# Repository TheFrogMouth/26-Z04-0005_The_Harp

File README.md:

# 26-Z04-0005 — The Harp

Frogmouth digital sympathetic-string guitar pedal. Up to 24 modelled strings
that nobody plays ring when the guitar sounds their note, retuned continuously
to the chord being played. STM32H750VBT6, AK4621EF codec, no SDRAM, relay
bypass, in a Hammond 125B on the Alchemist/Relic board and jack layout.

Status: **first schematic draft, board placed and mostly routed, 29 connections open.** Seven sheets generated from the Timekeeper's circuits and The Relic's bypass (190 parts, net-traced, drawn to the Frogmouth schematic standard, not yet opened in KiCad); board outline and 28 face/jack/bypass footprints placed from The Relic. Stereo in (TRS) and a 0.91 in OLED display added 2026-10-08; the PCB was synced to the schematic and every part placed on both sides on 2026-10-08 (scripted; one-board fit confirmed, see `docs/pcb-plan.md` *Placement*). First routing pass by script on 2026-10-09: GND to In1 and rails on In2 from every pad, analog and digital kept apart. Opened in KiCad 2026-10-10 (now the source of truth): power section re-placed and re-routed, every track at the Alchemist widths and at 0/45/90°, 29 connections left for KiCad (*Routing*). See `docs/pcb-plan.md` and `kicad/README.md`.

## Layout

| Path | Contents |
|------|----------|
| `docs/design-brief.md` | What the pedal is, engine, controls, bypass, cost target, decisions, open items |
| `docs/pcb-plan.md` | One-board plan and two-board fallback, face schedule, zoning, schematic sheets, pin budget, order of work |
| `docs/firmware-requirements.md` | Firmware requirements (draft): audio path, engine, controls, display, bypass, persistence, budgets, verification |
| `kicad/the_harp/` | KiCad 10 project: seven-sheet schematic, Relic-outline board |
| `Gerbers/` | Fabrication output, when generated |
| `firmware/the_harp/` | STM32H750 firmware |
| `Documents/` | Controlled LaTeX documents, one folder each |
| `bom/` | Generated BOM (`scripts/export_bom.py`, to be adapted from The Relic) |
| `scripts/harp_schematic/` | Schematic generator and net checker (first draft only; see its README) |
| `scripts/pcb_placement/` | PCB sync to the schematic and scripted placement (2026-10-08; see its README) |
| `scripts/oled_drawings/` | Face cut-out and OLED-to-PCB drawings in `docs/images/` |

The layout is the Frogmouth product repository standard
(`docs/repo-structure.md` in 26-F01-0001_Frogmouth).

## Conventions

Same as The Relic and The Alchemist: enclosure centre is the PCB drill/place
and grid origin at (148.5, 105); face X right, face Y up; jacks on the board
underside at the Alchemist's positions and heights; pots on the board;
momentary footswitches wired to pads; relay true bypass.

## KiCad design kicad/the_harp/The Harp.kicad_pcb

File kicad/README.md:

# KiCad project — The Harp

`the_harp/` is the KiCad 10 project. The board was seeded from The Relic
(2026-10-04); the schematic is **generated** by
`scripts/harp_schematic/build_layout.py` from the circuits of the Timekeeper
DSP board and The Relic's relay bypass (`harp_spec.py`) and a hand layout per
sheet (`layouts/`), drawn to the Frogmouth schematic standard
(`docs/schematic-standard.md` in 26-F01-0001_Frogmouth, 2026-10-07). Nothing
here has been opened in KiCad yet: run ERC first.

## Sheets

| Sheet | File |
|---|---|
| Root | `The Harp.kicad_sch` |
| Controls and LEDs | `Controls and LEDs.kicad_sch` |
| MCU (STM32H750VBT6, W25Q128) | `MCU.kicad_sch` |
| Power | `Power.kicad_sch` |
| Jacks and Bypass | `Jacks and Bypass.kicad_sch` |
| Codec (AK4621EF) | `Codec.kicad_sch` |
| ADC Driver (THS4522) | `ADC Driver.kicad_sch` |
| Analog In and Out (OPA1656, OPA1688) | `Analog In and Out.kicad_sch` |

What each sheet holds, the pin map and the deliberate differences from the
Timekeeper are in `docs/pcb-plan.md`. The Relic's `Power and IO` sheet is
gone: its relay bypass is redrawn on Jacks and Bypass with the same
designators, and its regulators are replaced by the Timekeeper's buck and LDO.

## Board

The Relic's 56 × 90 mm outline with the DC tab, four-layer stack, GND zone
and 125B guides. 26 footprints are placed: the four pots, three toggles, the
effect LED, the five jacks (DC, IN, OUT L, OUT R, EXP), the relay and its
driver, the effect-LED driver and the bypass footswitch pads. The four
1/4 in jacks and the relay were replaced on 2026-10-05 with The Alchemist's
NMJ6HCD2 and G6K-2F-Y footprints at its positions. On 2026-10-06 the face
moved to The Alchemist's layout: RV104 and RV106 removed, the three toggles
on the Taiway 100-DP6 footprint at (−20, +13), (0, −5) and (+20, +13) (Retune moved to (0, −24) on 2026-10-09), the
bypass footswitch on hand-solder pads, and R405 / D402 moved off J403's
rear pads. The Relic's
regulator parts (C401–C407, D401, R401–R403, U401, U402) were removed. On
2026-10-08 the board was synced to the schematic (see step 2 below): every
footprint is linked to its symbol with its pad nets, the twelve note LEDs
and their resistors are gone. All 181 footprints were then placed on the
top side by script (`scripts/pcb_placement/`, `docs/pcb-plan.md` *Placement*).

## First steps in KiCad

1. Open `The Harp.kicad_pro`, open every sheet once, run ERC. Expect
   cosmetic warnings (label placement, overlapping text); anything about
   power pins or unconnected pins is real, report it.
2. The board was synced to the schematic on 2026-10-08 without KiCad (no
   KiCad in that session): 181 footprints (190 symbol units), each linked to its symbol, values
   and pad nets checked pin by pin against `harp_spec.py`. Run Tools → Update PCB from
   Schematic once anyway: it should report no changes apart from net
   renames (KiCad names unlabelled nets `Net-(...)`) and footprint library
   refreshes. Anything else it reports is a sync miss: note it.
3. Every part is placed on both sides (scripted, 2026-10-08; see *Placement*
   in `docs/pcb-plan.md`). Look it over, then run DRC.
4. The board was routed by script on 2026-10-09 (`scripts/pcb_routing/`,
   *Routing* in `docs/pcb-plan.md`): GND vias per the Relic rule, rails on
   In2. On 2026-10-10 the power section was re-placed and re-routed and
   every track brought to the Alchemist widths (0.254 / 0.508 / 0.762 /
   1.0 mm, digital 0.1524) and to 0/45/90°. Fill the In1 GND zone (B), finish the 29 open
   connections listed there, then DRC. The net classes (GND, Rail, Power,
   Audio, Digital, Control, clearance 0.1524) are in the project.

Once the schematic has been edited in KiCad, the KiCad files are the source
of truth; do not re-run the generator over them (see
`scripts/harp_schematic/README.md`).

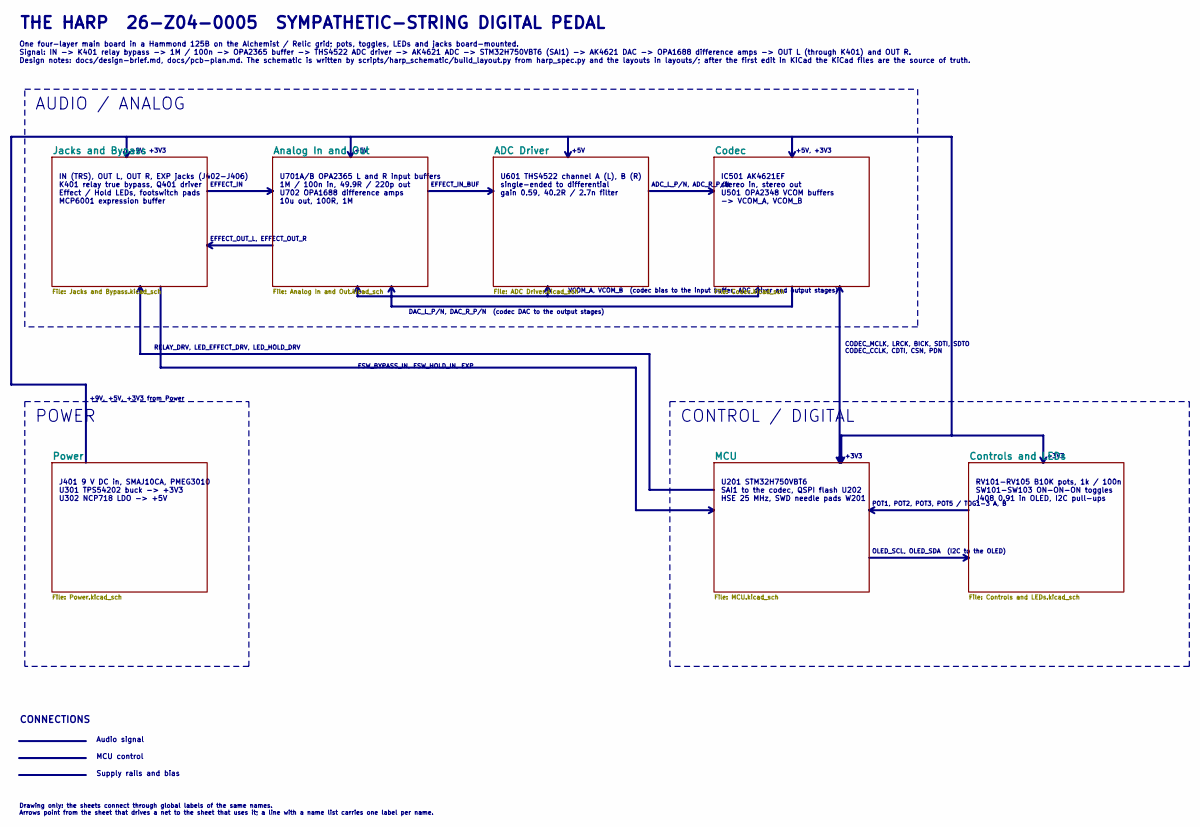
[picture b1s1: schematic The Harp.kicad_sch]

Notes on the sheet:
RELAY_DRV, LED_EFFECT_DRV, LED_HOLD_DRV
+5V, +3V3
J401 9 V DC in, SMAJ10CA, PMEG3010 U301 TPS54202 buck -> +3V3 U302 NCP718 LDO -> +5V
CONTROL / DIGITAL
+5V
EFFECT_OUT_L, EFFECT_OUT_R
DAC_L_P/N, DAC_R_P/N (codec DAC to the output stages)
THE HARP 26-Z04-0005 SYMPATHETIC-STRING DIGITAL PEDAL
FSW_BYPASS_IN, FSW_HOLD_IN, EXP
+9V, +5V, +3V3 from Power
Supply rails and bias
IC501 AK4621EF stereo in, stereo out U501 OPA2348 VCOM buffers -> VCOM_A, VCOM_B
POT1, POT2, POT3, POT5 / TOG1-3 A, B
EFFECT_IN_BUF
U601 THS4522 channel A (L), B (R) single-ended to differential gain 0.59, 40.2R / 2.7n filter
OLED_SCL, OLED_SDA (I2C to the OLED)
U701A/B OPA2365 L and R input buffers 1M / 100n in, 49.9R / 220p out U702 OPA1688 difference amps 10u out, 100R, 1M
Audio signal
+9V, +3V3
One four-layer main board in a Hammond 125B on the Alchemist / Relic grid; pots, toggles, LEDs and jacks board-mounted. Signal: IN -> K401 relay bypass -> 1M / 100n -> OPA2365 buffer -> THS4522 ADC driver -> AK4621 ADC -> STM32H750VBT6 (SAI1) -> AK4621 DAC -> OPA1688 difference amps -> OUT L (throu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
+3V3
U201 STM32H750VBT6 SAI1 to the codec, QSPI flash U202 HSE 25 MHz, SWD needle pads W201
MCU control
CODEC_MCLK, LRCK, BICK, SDTI, SDTO CODEC_CCLK, CDTI, CSN, PDN
POWER
IN (TRS), OUT L, OUT R, EXP jacks (J402-J406) K401 relay true bypass, Q401 driver Effect / Hold LEDs, footswitch pads MCP6001 expression buffer
RV101-RV105 B10K pots, 1k / 100n SW101-SW103 ON-ON-ON toggles J408 0.91 in OLED, I2C pull-ups
AUDIO / ANALOG
EFFECT_IN
VCOM_A, VCOM_B (codec bias to the input buffer, ADC driver and output stages)
CONNECTIONS
ADC_L_P/N, ADC_R_P/N
Drawing only: the sheets connect through global labels of the same names. Arrows point from the sheet that drives a net to the sheet that uses it; a line with a name list carries one label per name.

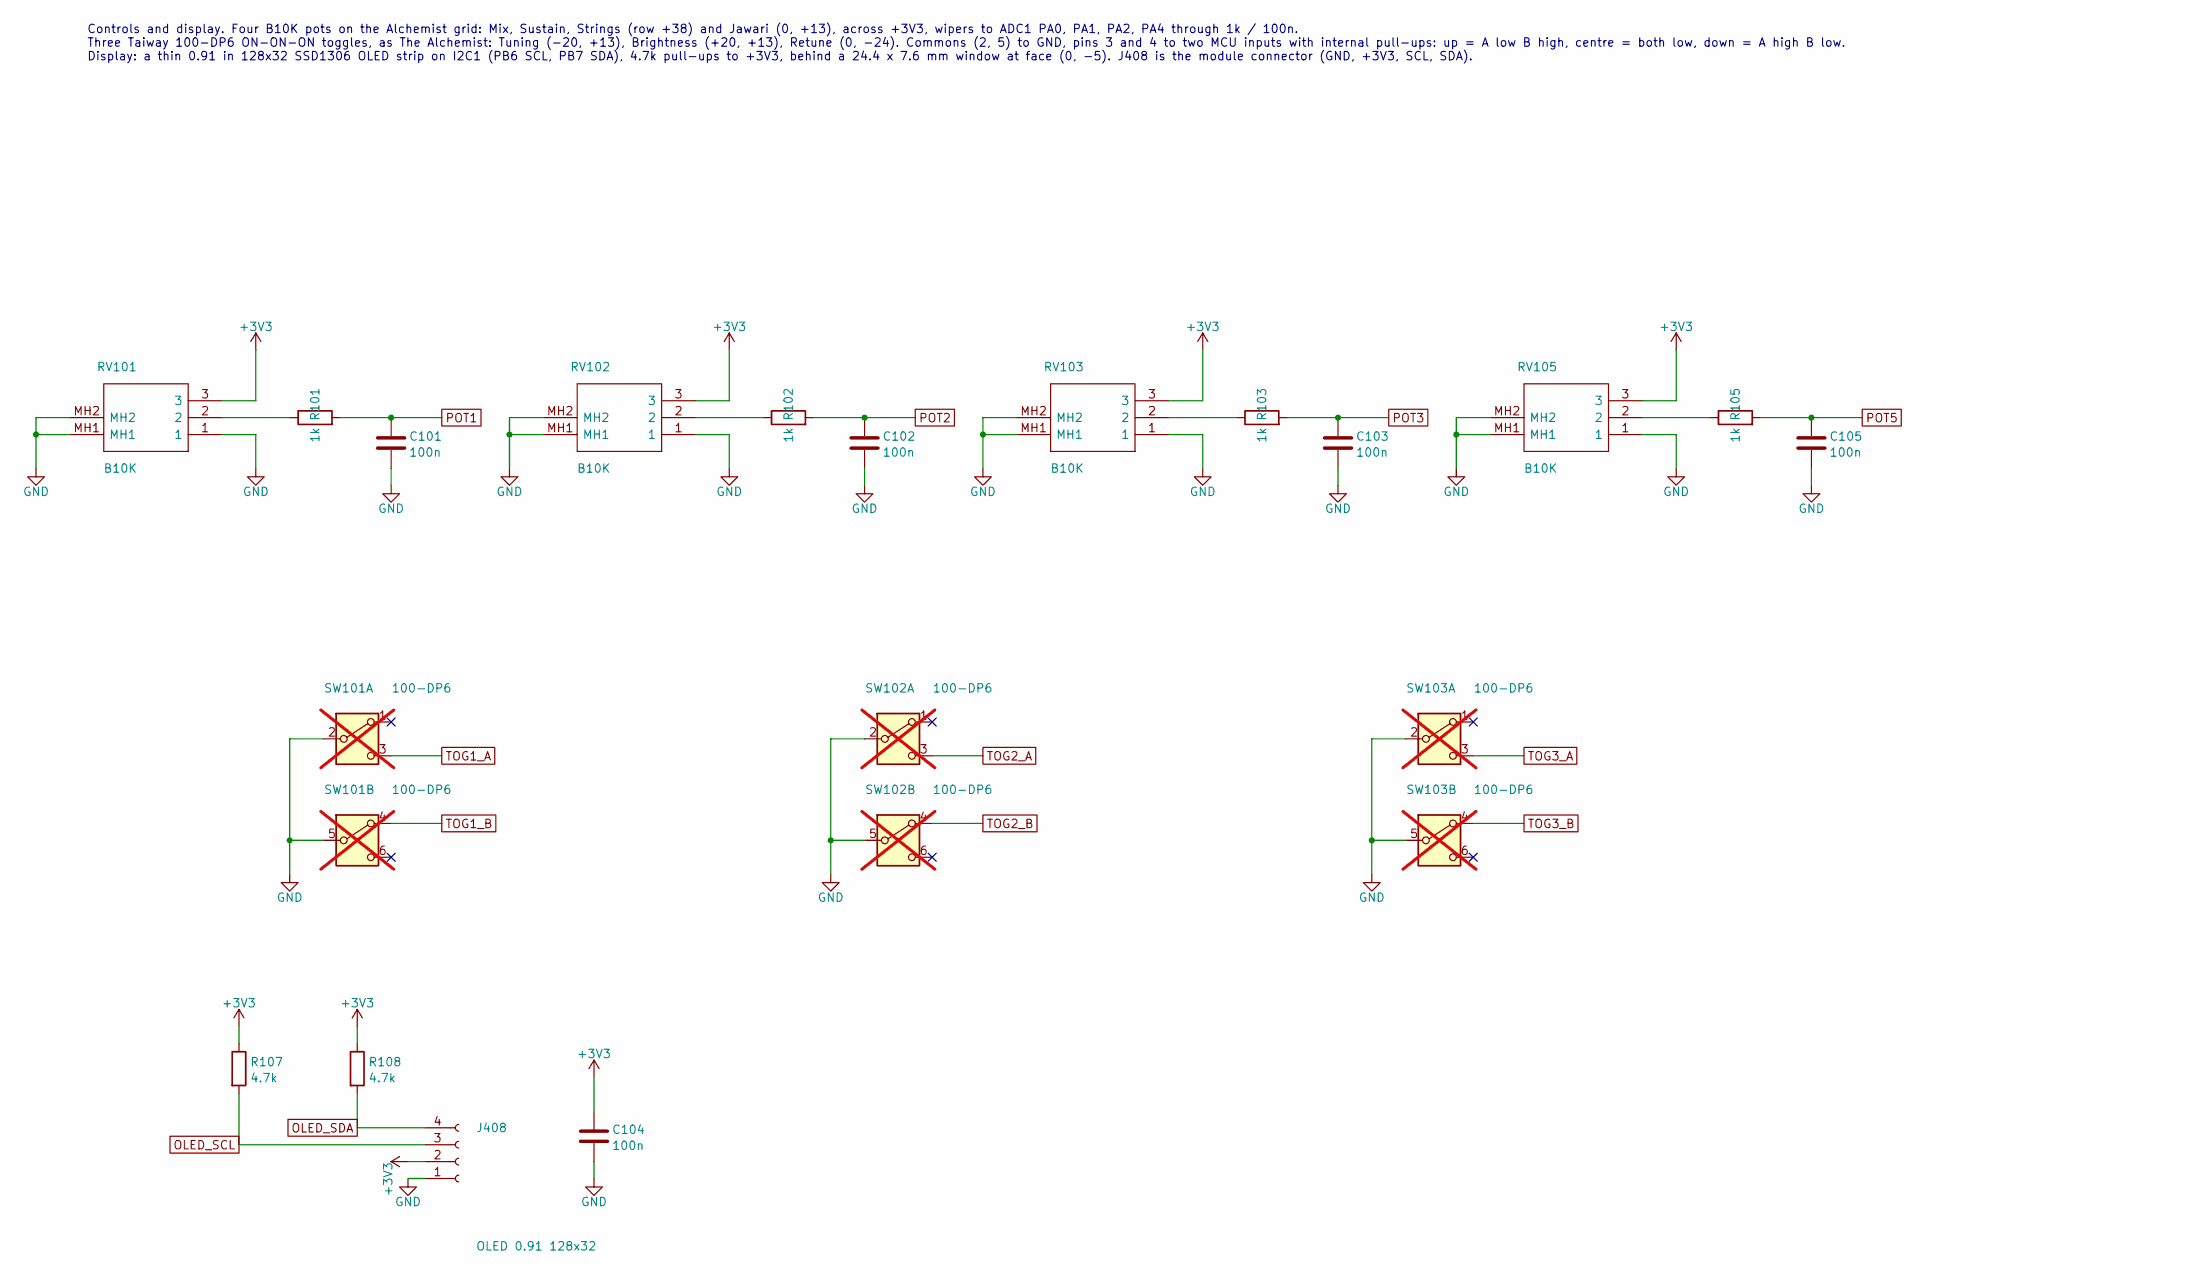
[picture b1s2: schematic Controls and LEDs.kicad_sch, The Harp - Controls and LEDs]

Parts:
C101, C102, C103, C104, C105: 100n; C_0603_1608Metric
J408: OLED 0.91 128x32; JST_SH_SM04B-SRSS-TB_1x04-1MP_P1.00mm_Horizontal; Mfg Part # SM04B-SRSS-TB
R101, R102, R103, R105: 1k; R_0603_1608Metric
R107, R108: 4.7k; R_0603_1608Metric
RV101, RV102, RV103, RV105: B10K; RD901F4015R1B10K00DL1; Mfg Part # RD901F-40-15R1-B10K; LCSC C20619174
SW101, SW102, SW103: 100-DP6; 100DP3T1B2M2QE; Mfg Part # 100-DP6-T200B1M2QE; not fitted

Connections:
+3V3: C104.1, J408.2, R107.1, R108.1, RV101.3, RV102.3, RV103.3, RV105.3; also elsewhere on the board
GND: C101.2, C102.2, C103.2, C104.2, C105.2, J408.1, RV101.1, RV101.MH1, RV101.MH2, RV102.1, RV102.MH1, RV102.MH2, RV103.1, RV103.MH1, RV103.MH2, RV105.1, RV105.MH1, RV105.MH2, SW101.2 (B), SW101.5 (B), SW102.2 (B), SW102.5 (B), SW103.2 (B), SW103.5 (B); also elsewhere on the board
unnamed: R101.1, RV101.2
unnamed: R102.1, RV102.2
unnamed: R103.1, RV103.2
unnamed: R105.1, RV105.2
OLED_SCL: J408.3, R107.2; also elsewhere on the board
OLED_SDA: J408.4, R108.2; also elsewhere on the board
POT1: C101.1, R101.2; also elsewhere on the board
POT2: C102.1, R102.2; also elsewhere on the board
POT3: C103.1, R103.2; also elsewhere on the board
POT5: C105.1, R105.2; also elsewhere on the board
TOG1_A: SW101.3 (C); also elsewhere on the board
TOG1_B: SW101.4 (A); also elsewhere on the board
TOG2_A: SW102.3 (C); also elsewhere on the board
TOG2_B: SW102.4 (A); also elsewhere on the board
TOG3_A: SW103.3 (C); also elsewhere on the board
TOG3_B: SW103.4 (A); also elsewhere on the board

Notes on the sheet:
Controls and display. Four B10K pots on the Alchemist grid: Mix, Sustain, Strings (row +38) and Jawari (0, +13), across +3V3, wipers to ADC1 PA0, PA1, PA2, PA4 through 1k / 100n. Three Taiway 100-DP6 ON-ON-ON toggles, as The Alchemist: Tuning (-20, +13), Brightness (+20, +13), Retune (0, -24). Comm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

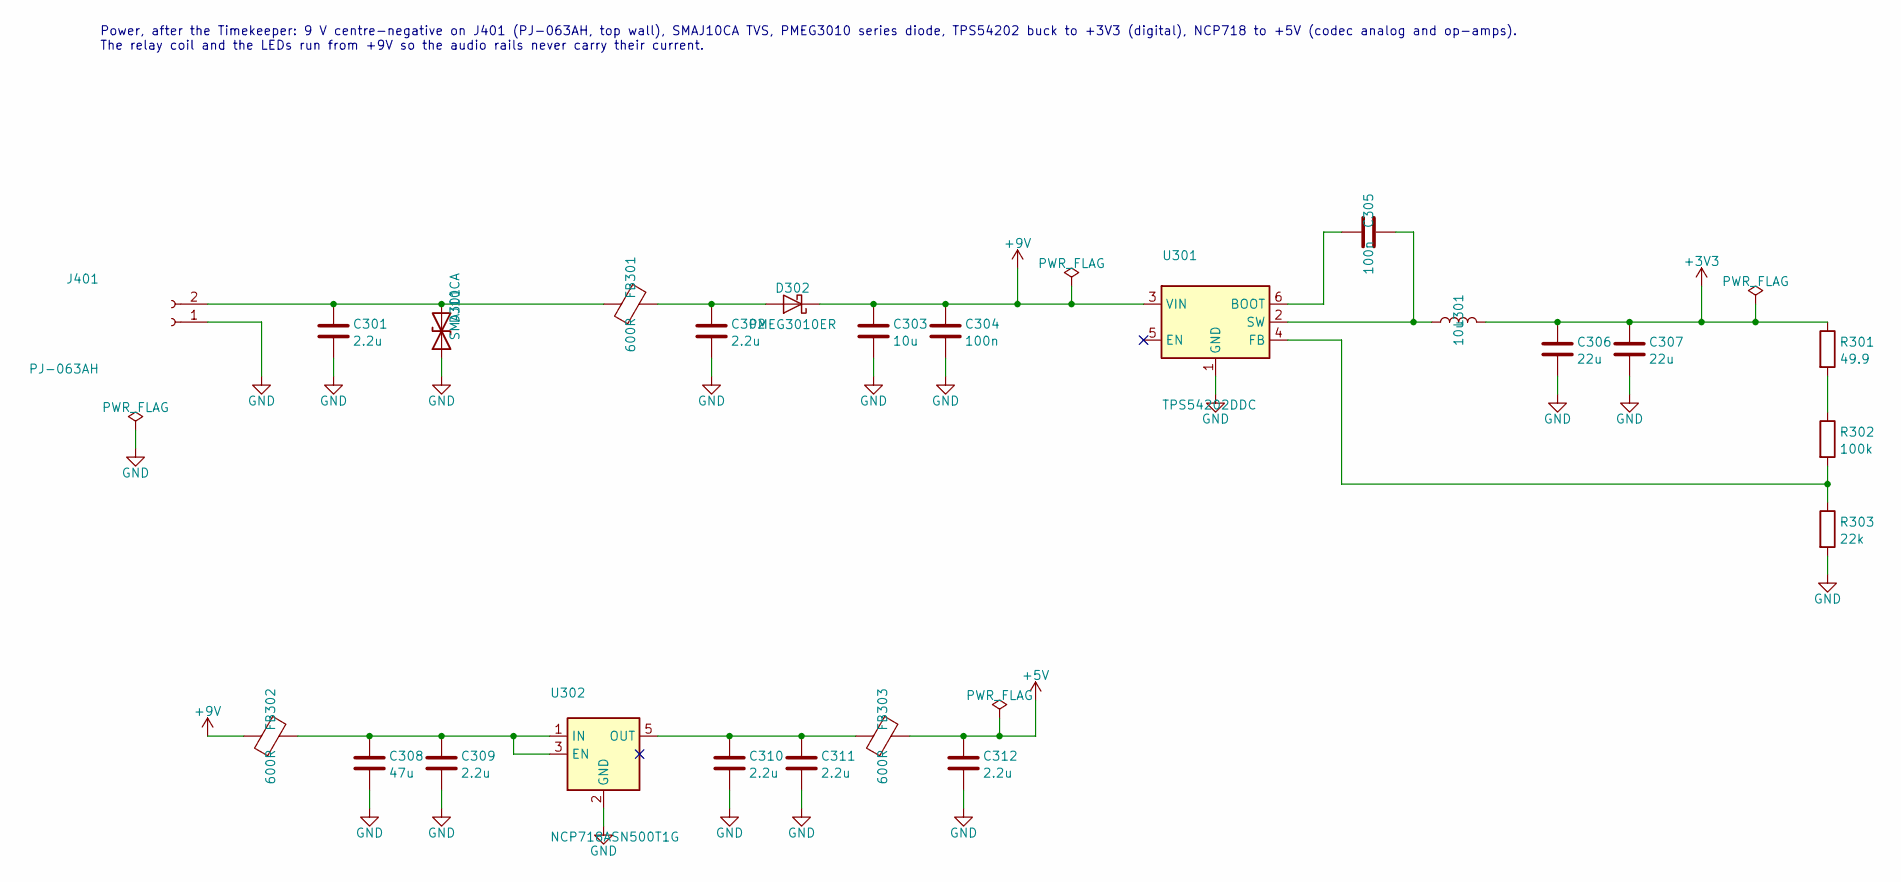
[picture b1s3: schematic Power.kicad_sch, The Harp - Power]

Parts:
C301, C302, C309, C310, C311, C312: 2.2u; C_0603_1608Metric
C303: 10u; C_1206_3216Metric
C304, C305: 100n; C_0603_1608Metric
C306, C307: 22u; C_1210_3225Metric
C308: 47u; C_1210_3225Metric
D301: SMAJ10CA; D_SMA; Mfg Part # SMAJ10CA
D302: PMEG3010ER; Nexperia_CFP3_SOD-123W; Mfg Part # PMEG3010ER,115
FB301, FB302, FB303: 600R; L_0603_1608Metric
J401: PJ-063AH; BarrelJack_CUI_PJ-063AH_Horizontal; Mfg Part # PJ-063AH; LCSC C22434582
L301: 10u; L_APV_ANR5020
R301: 49.9; R_0603_1608Metric
R302: 100k; R_0603_1608Metric
R303: 22k; R_0603_1608Metric
U301: TPS54202DDC; SOT-23-6; Mfg Part # TPS54202DDCR
U302: NCP718ASN500T1G; TSOT-23-5; Mfg Part # NCP718ASN500T1G; LCSC C603786

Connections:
+3V3: C306.1, C307.1, L301.2, R301.1; also elsewhere on the board
+5V: C312.1, FB303.2; also elsewhere on the board
+9V: C303.1, C304.1, D302.1 (K), FB302.1, U301.3 (VIN); also elsewhere on the board
GND: C301.2, C302.2, C303.2, C304.2, C306.2, C307.2, C308.2, C309.2, C310.2, C311.2, C312.2, D301.1 (A1), J401.1, R303.2, U301.1 (GND), U302.2 (GND); also elsewhere on the board
unnamed: C301.1, D301.2 (A2), FB301.1, J401.2
unnamed: C302.1, D302.2 (A), FB301.2
unnamed: R301.2, R302.1
unnamed: C305.1, U301.6 (BOOT)
unnamed: R302.2, R303.1, U301.4 (FB)
unnamed: C305.2, L301.1, U301.2 (SW)
unnamed: C308.1, C309.1, FB302.2, U302.1 (IN), U302.3 (EN)
unnamed: C310.1, C311.1, FB303.1, U302.5 (OUT)

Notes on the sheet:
Power, after the Timekeeper: 9 V centre-negative on J401 (PJ-063AH, top wall), SMAJ10CA TVS, PMEG3010 series diode, TPS54202 buck to +3V3 (digital), NCP718 to +5V (codec analog and op-amps). The relay coil and the LEDs run from +9V so the audio rails never carry their current.

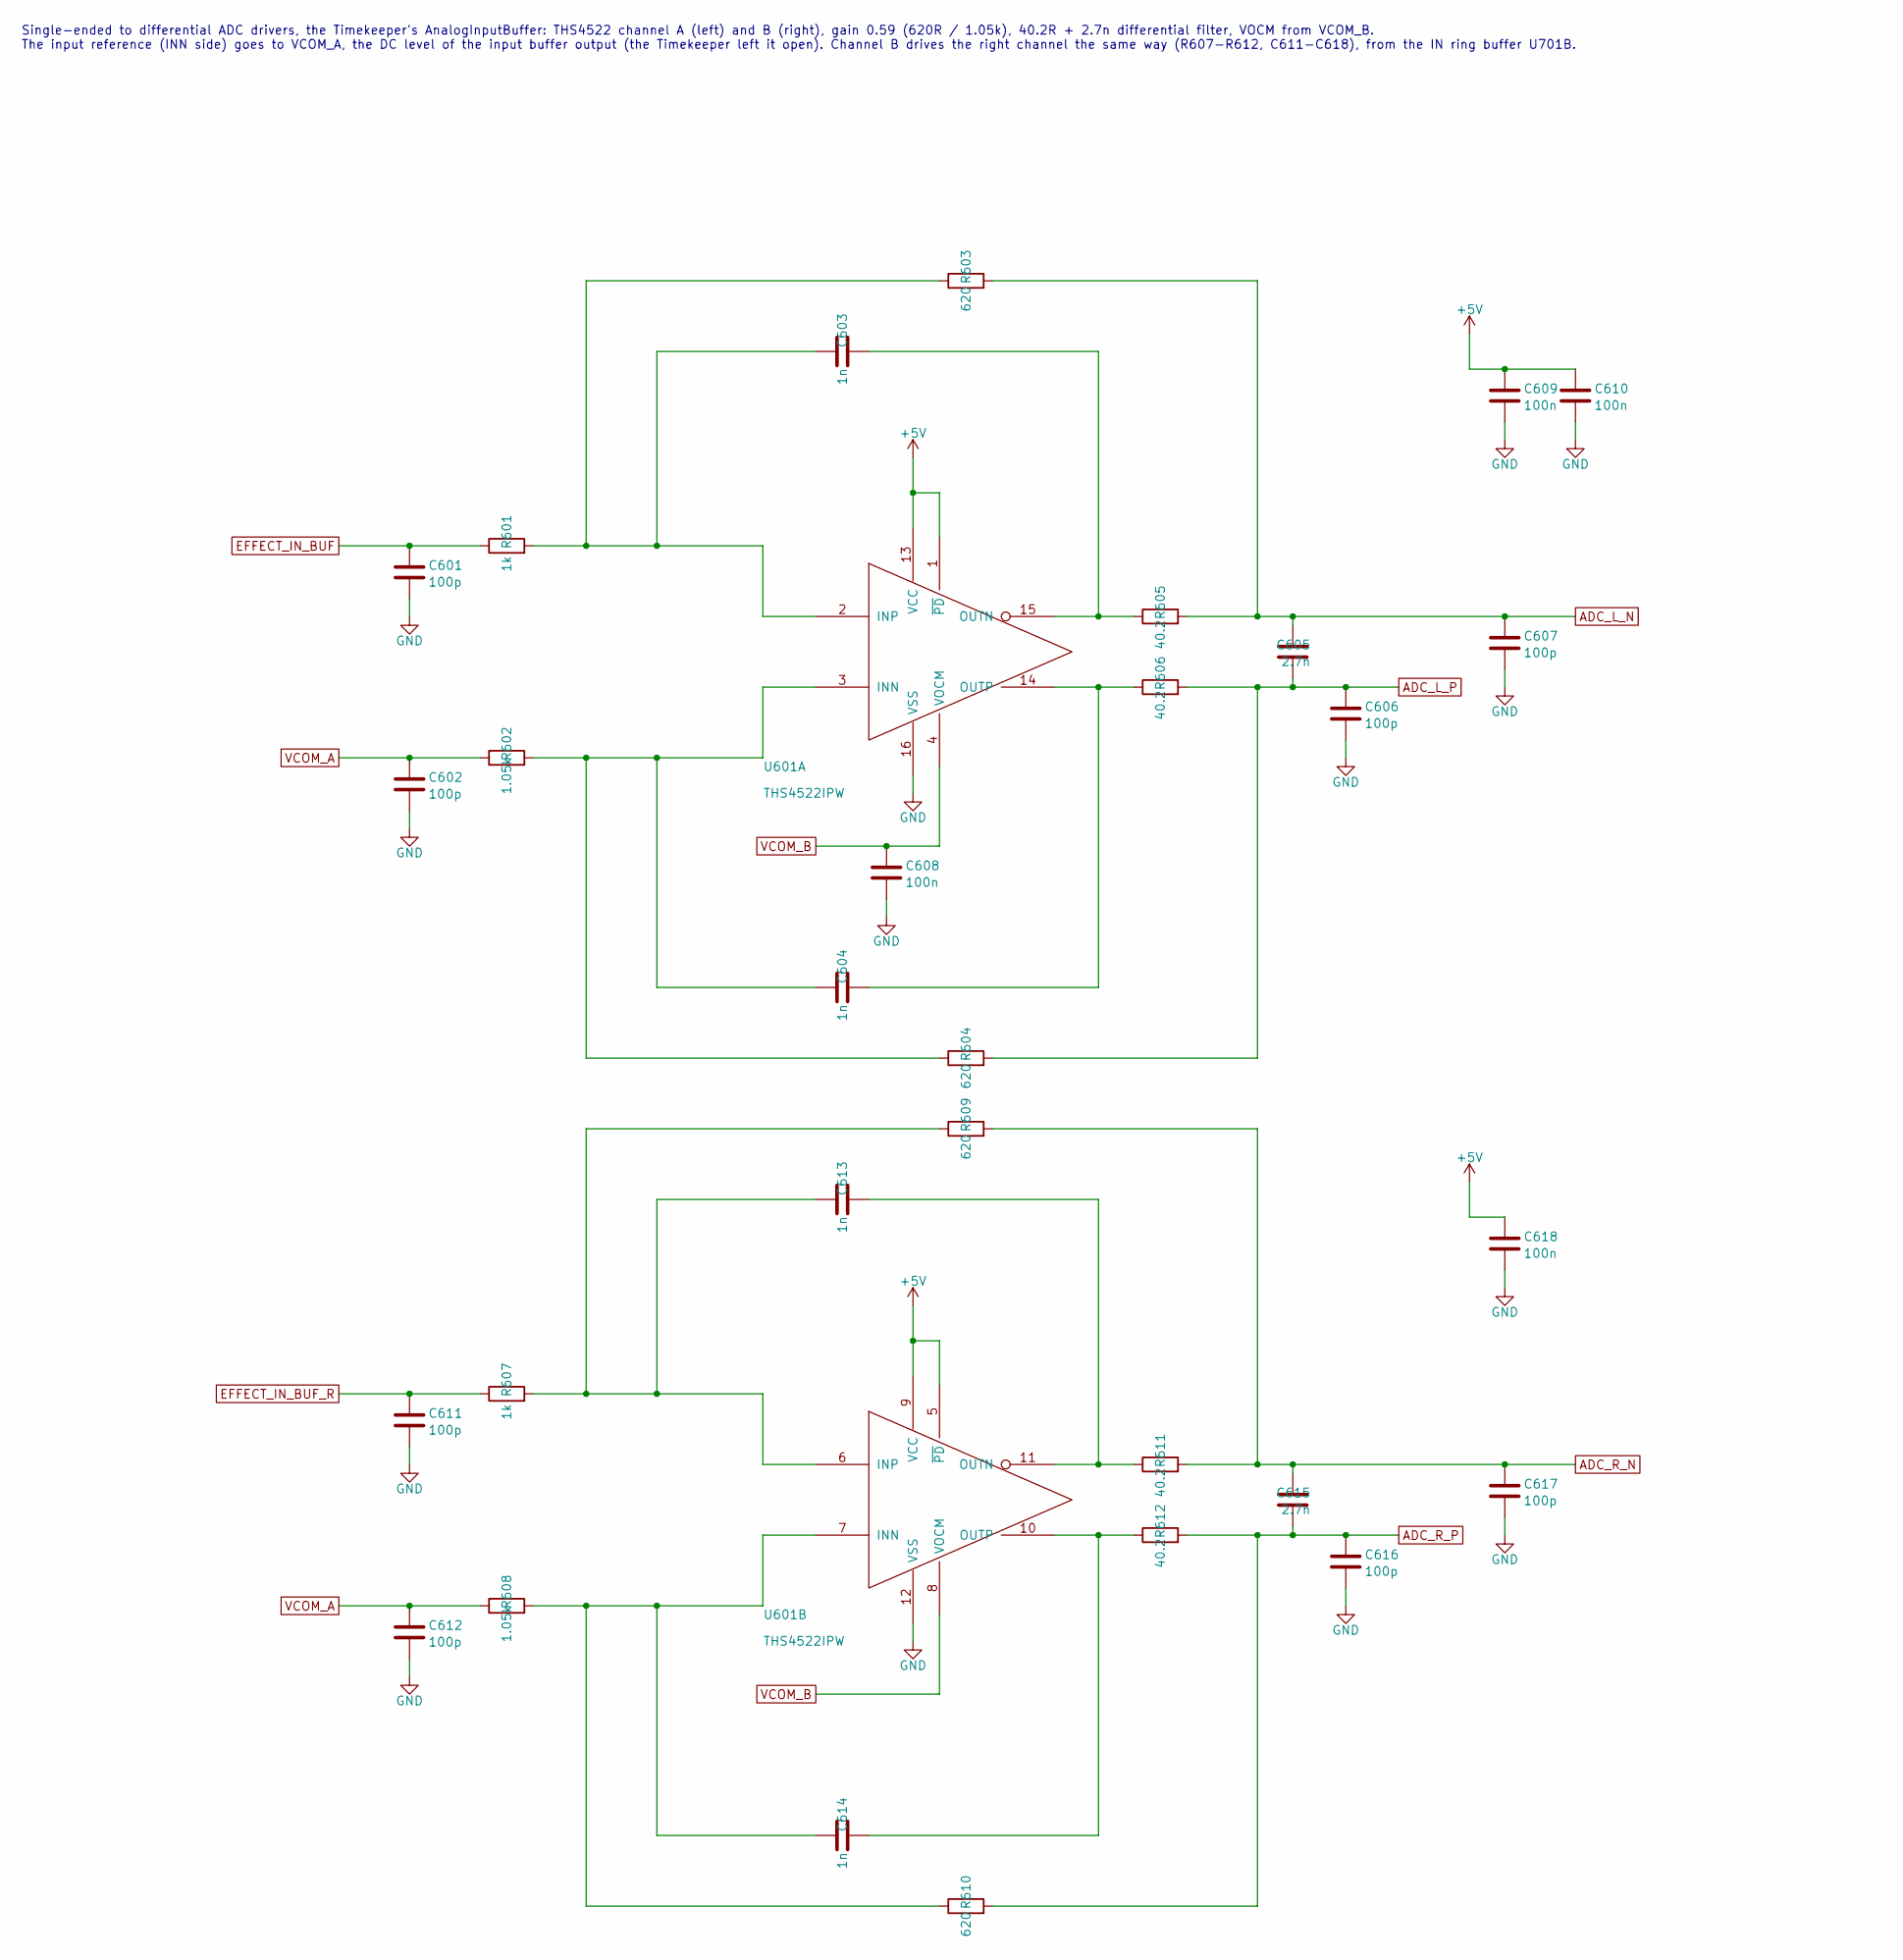
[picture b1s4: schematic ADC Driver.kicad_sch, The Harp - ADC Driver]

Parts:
C601, C602, C606, C607, C611, C612, C616, C617: 100p; C_0603_1608Metric
C603, C604, C613, C614: 1n; C_0603_1608Metric
C605, C615: 2.7n; C_0603_1608Metric
C608, C609, C610, C618: 100n; C_0603_1608Metric
R601, R607: 1k; R_0603_1608Metric
R602, R608: 1.05k; R_0603_1608Metric
R603, R604, R609, R610: 620; R_0603_1608Metric
R605, R606, R611, R612: 40.2; R_0603_1608Metric
U601: THS4522IPW; TSSOP-16_4.4x5mm_P0.65mm; Mfg Part # THS4522IPWR

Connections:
+5V: C609.1, C610.1, C618.1, U601.1 (~PD), U601.5 (~PD), U601.9 (VCC), U601.13 (VCC); also elsewhere on the board
ADC_L_N: C605.2, C607.1, R603.2, R605.2; also elsewhere on the board
ADC_L_P: C605.1, C606.1, R604.2, R606.2; also elsewhere on the board
ADC_R_N: C615.2, C617.1, R609.2, R611.2; also elsewhere on the board
ADC_R_P: C615.1, C616.1, R610.2, R612.2; also elsewhere on the board
EFFECT_IN_BUF: C601.1, R601.1; also elsewhere on the board
EFFECT_IN_BUF_R: C611.1, R607.1; also elsewhere on the board
GND: C601.2, C602.2, C606.2, C607.2, C608.2, C609.2, C610.2, C611.2, C612.2, C616.2, C617.2, C618.2, U601.12 (VSS), U601.16 (VSS); also elsewhere on the board
unnamed: C604.1, R602.2, R604.1, U601.3 (INN)
unnamed: C603.1, R601.2, R603.1, U601.2 (INP)
unnamed: C603.2, R605.1, U601.15 (OUTN)
unnamed: C604.2, R606.1, U601.14 (OUTP)
unnamed: C614.1, R608.2, R610.1, U601.7 (INN)
unnamed: C613.1, R607.2, R609.1, U601.6 (INP)
unnamed: C613.2, R611.1, U601.11 (OUTN)
unnamed: C614.2, R612.1, U601.10 (OUTP)
VCOM_A: C602.1, C612.1, R602.1, R608.1; also elsewhere on the board
VCOM_B: C608.1, U601.4 (VOCM), U601.8 (VOCM); also elsewhere on the board

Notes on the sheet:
Single-ended to differential ADC drivers, the Timekeeper's AnalogInputBuffer: THS4522 channel A (left) and B (right), gain 0.59 (620R / 1.05k), 40.2R + 2.7n differential filter, VOCM from VCOM_B. The input reference (INN side) goes to VCOM_A, the DC level of the input buffer output (the Timekeeper 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

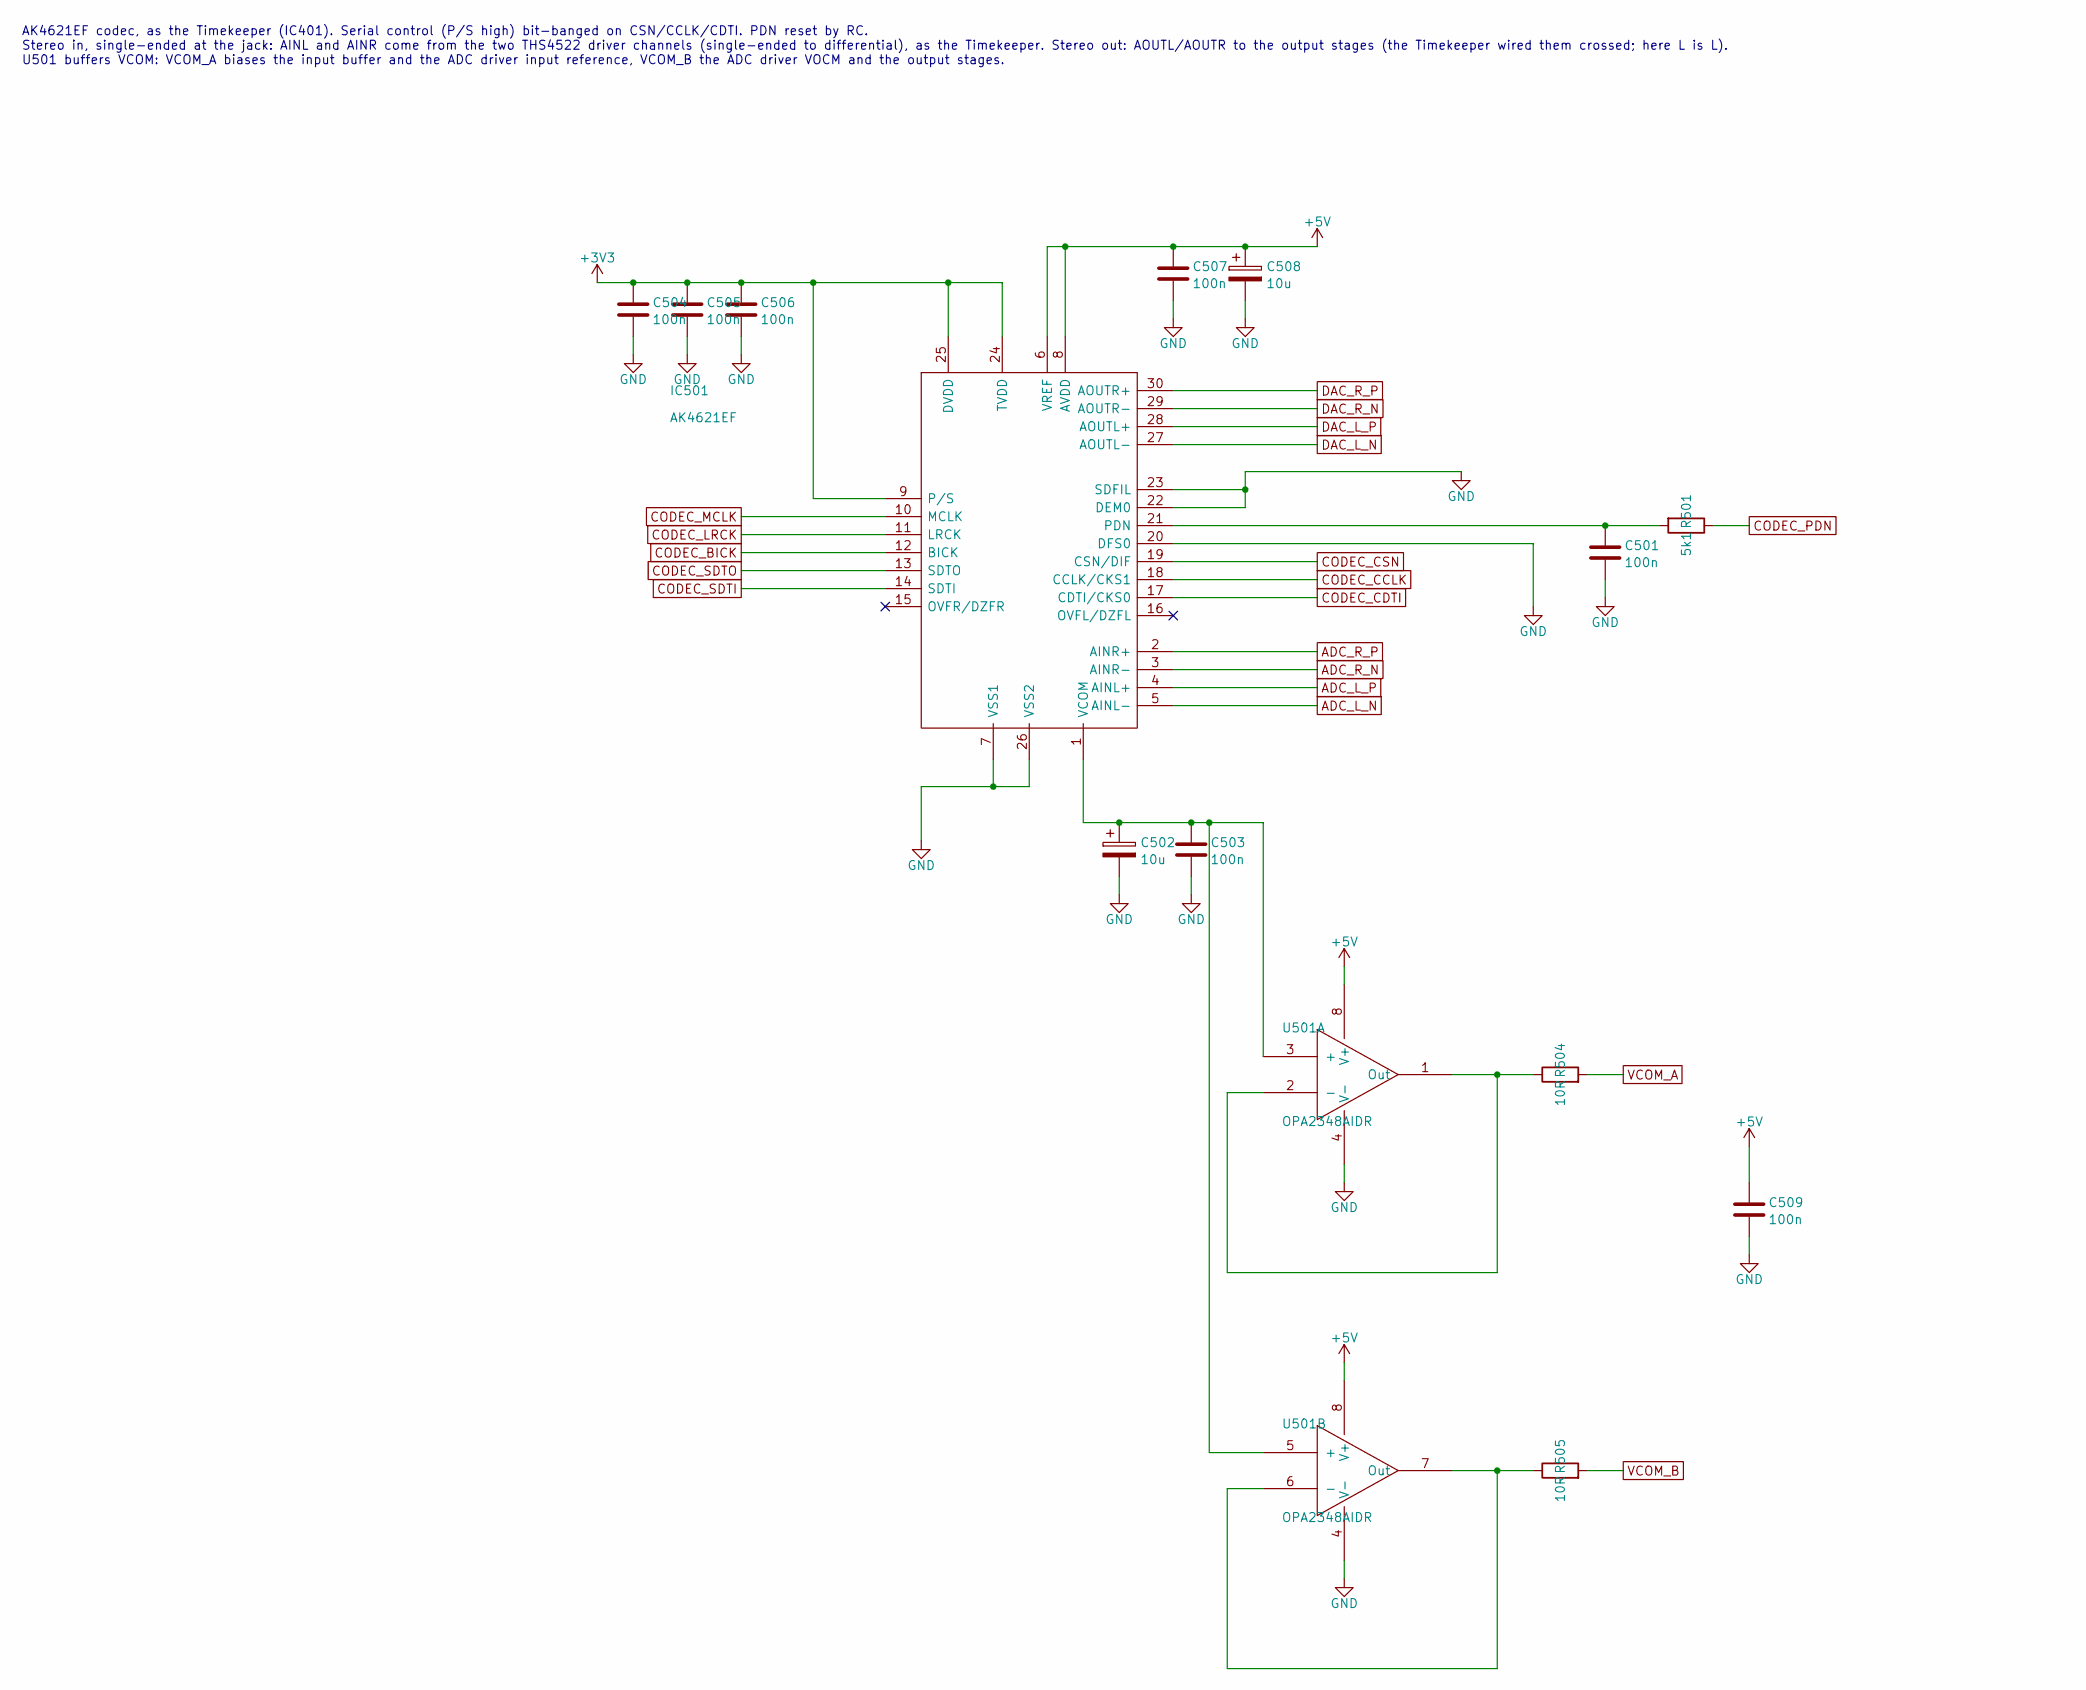
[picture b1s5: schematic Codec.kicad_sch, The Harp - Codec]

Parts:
C501, C503, C504, C505, C506, C507, C509: 100n; C_0603_1608Metric
C502, C508: 10u; CP_Elec_4x5.8
IC501: AK4621EF; SOP65P760X150-30N; Mfg Part # AK4621EF
R501: 5k1; R_0603_1608Metric
R504, R505: 10R; R_0603_1608Metric
U501: OPA2348AIDR; SOIC-8_3.9x4.9mm_P1.27mm; Mfg Part # OPA2348AIDR

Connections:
+3V3: C504.1, C505.1, C506.1, IC501.9 (P/S), IC501.24 (TVDD), IC501.25 (DVDD); also elsewhere on the board
+5V: C507.1, C508.1, C509.1, IC501.6 (VREF), IC501.8 (AVDD), U501.8 (V+); also elsewhere on the board
ADC_L_N: IC501.5 (AINL-); also elsewhere on the board
ADC_L_P: IC501.4 (AINL+); also elsewhere on the board
ADC_R_N: IC501.3 (AINR-); also elsewhere on the board
ADC_R_P: IC501.2 (AINR+); also elsewhere on the board
CODEC_BICK: IC501.12 (BICK); also elsewhere on the board
CODEC_CCLK: IC501.18 (CCLK/CKS1); also elsewhere on the board
CODEC_CDTI: IC501.17 (CDTI/CKS0); also elsewhere on the board
CODEC_CSN: IC501.19 (CSN/DIF); also elsewhere on the board
CODEC_LRCK: IC501.11 (LRCK); also elsewhere on the board
CODEC_MCLK: IC501.10 (MCLK); also elsewhere on the board
CODEC_PDN: R501.1; also elsewhere on the board
CODEC_SDTI: IC501.14 (SDTI); also elsewhere on the board
CODEC_SDTO: IC501.13 (SDTO); also elsewhere on the board
DAC_L_N: IC501.27 (AOUTL-); also elsewhere on the board
DAC_L_P: IC501.28 (AOUTL+); also elsewhere on the board
DAC_R_N: IC501.29 (AOUTR-); also elsewhere on the board
DAC_R_P: IC501.30 (AOUTR+); also elsewhere on the board
GND: C501.2, C502.2, C503.2, C504.2, C505.2, C506.2, C507.2, C508.2, C509.2, IC501.7 (VSS1), IC501.20 (DFS0), IC501.22 (DEM0), IC501.23 (SDFIL), IC501.26 (VSS2), U501.4 (V-); also elsewhere on the board
unnamed: C501.1, IC501.21 (PDN), R501.2
unnamed: C502.1, C503.1, IC501.1 (VCOM), U501.3 (+), U501.5 (+)
unnamed: R504.1, U501.1 (Out), U501.2 (-)
unnamed: R505.1, U501.6 (-), U501.7 (Out)
VCOM_A: R504.2; also elsewhere on the board
VCOM_B: R505.2; also elsewhere on the board

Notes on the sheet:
AK4621EF codec, as the Timekeeper (IC401). Serial control (P/S high) bit-banged on CSN/CCLK/CDTI. PDN reset by RC. Stereo in, single-ended at the jack: AINL and AINR come from the two THS4522 driver channels (single-ended to differential), as the Timekeeper. Stereo out: AOUTL/AOUTR to the output st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
